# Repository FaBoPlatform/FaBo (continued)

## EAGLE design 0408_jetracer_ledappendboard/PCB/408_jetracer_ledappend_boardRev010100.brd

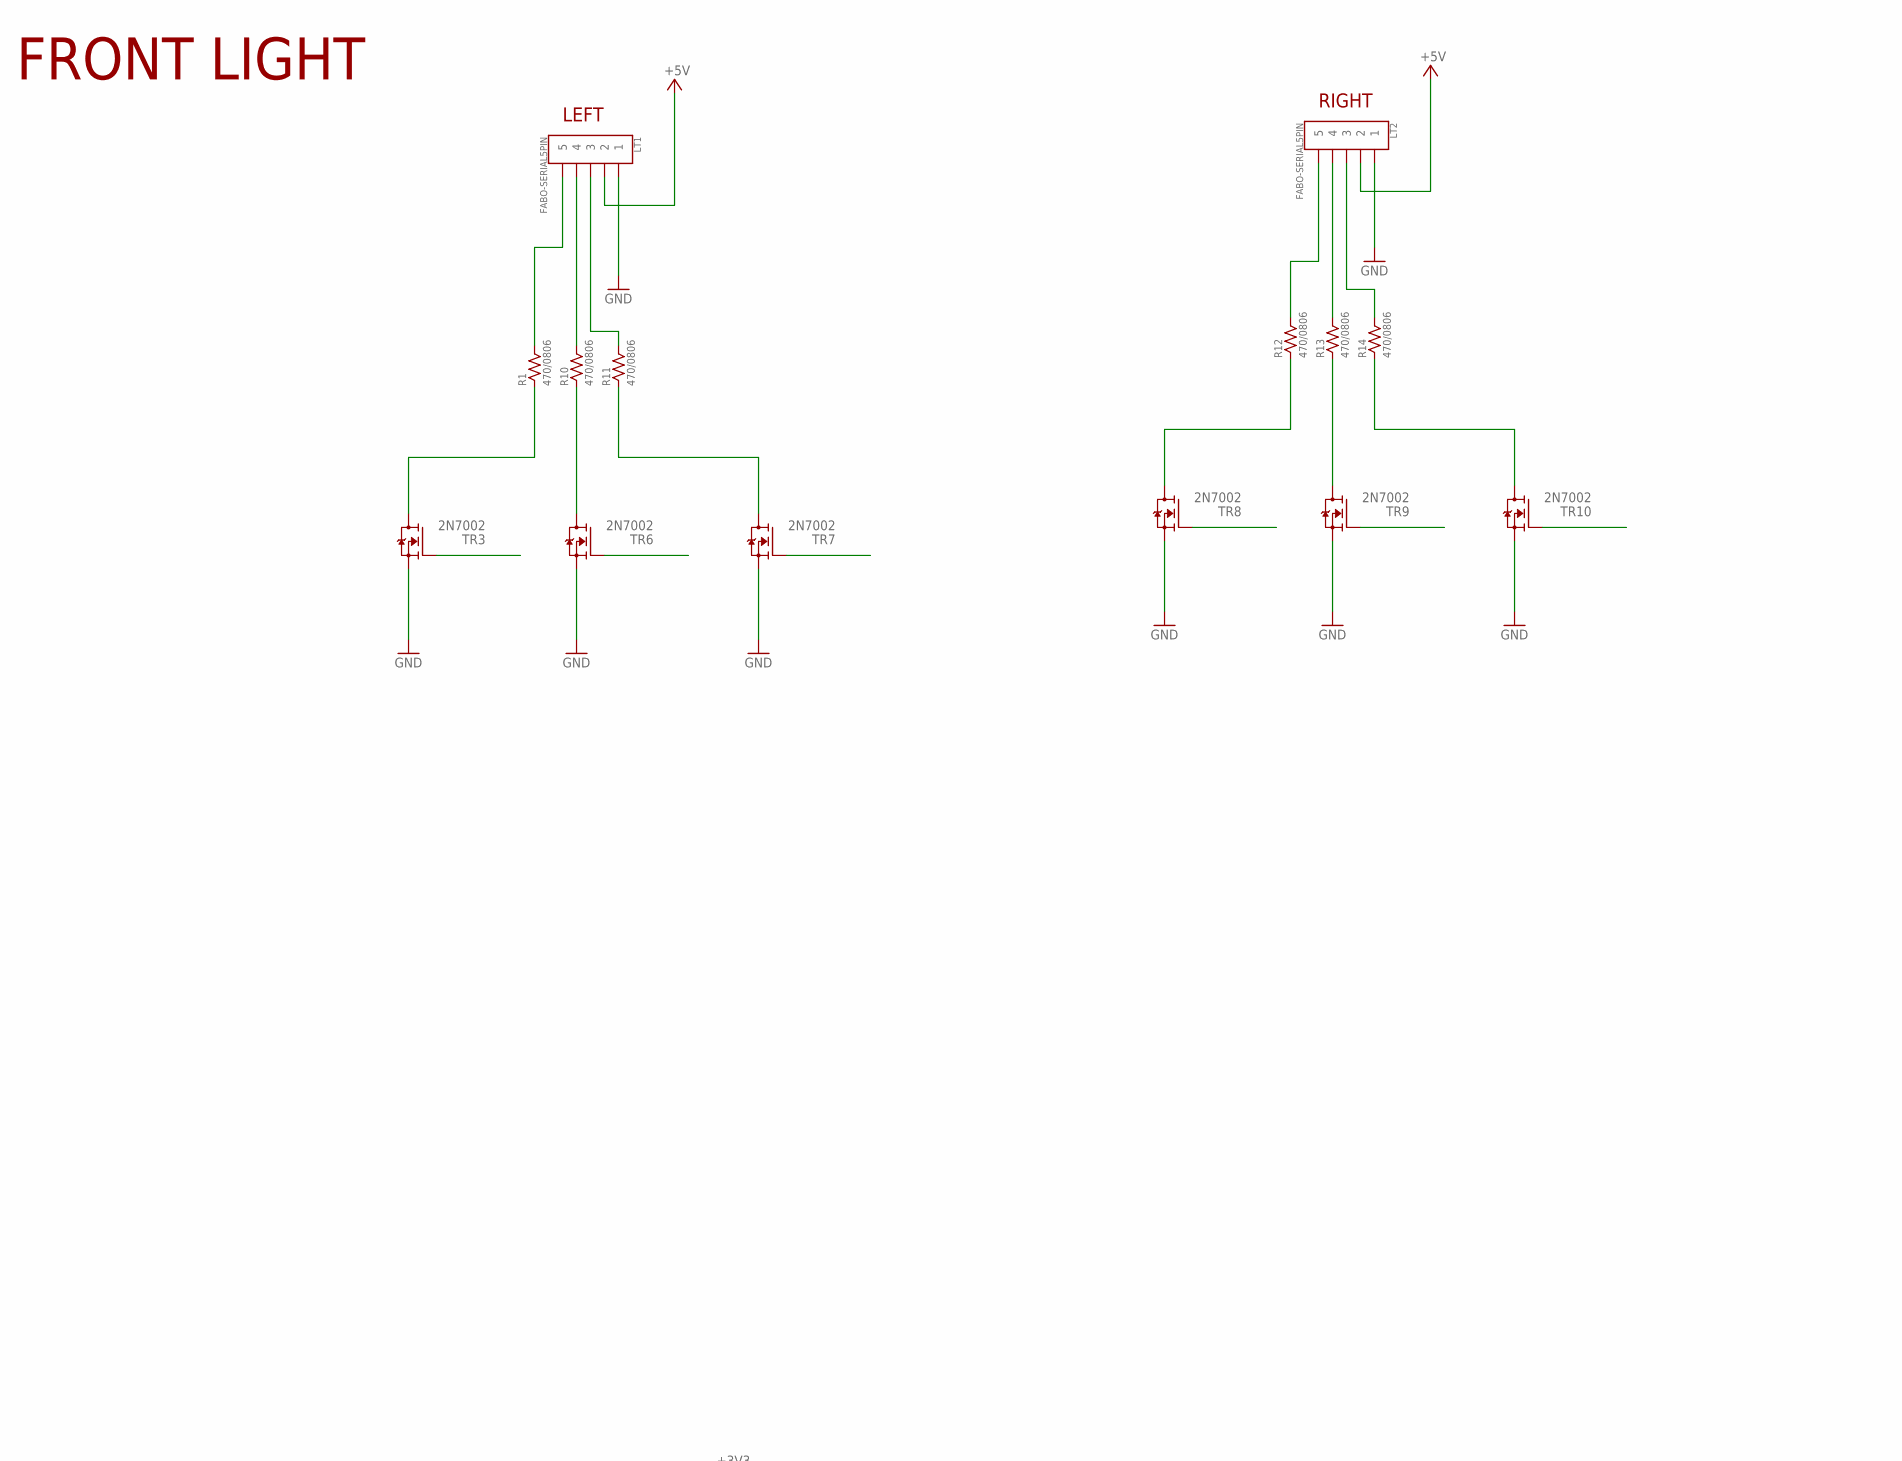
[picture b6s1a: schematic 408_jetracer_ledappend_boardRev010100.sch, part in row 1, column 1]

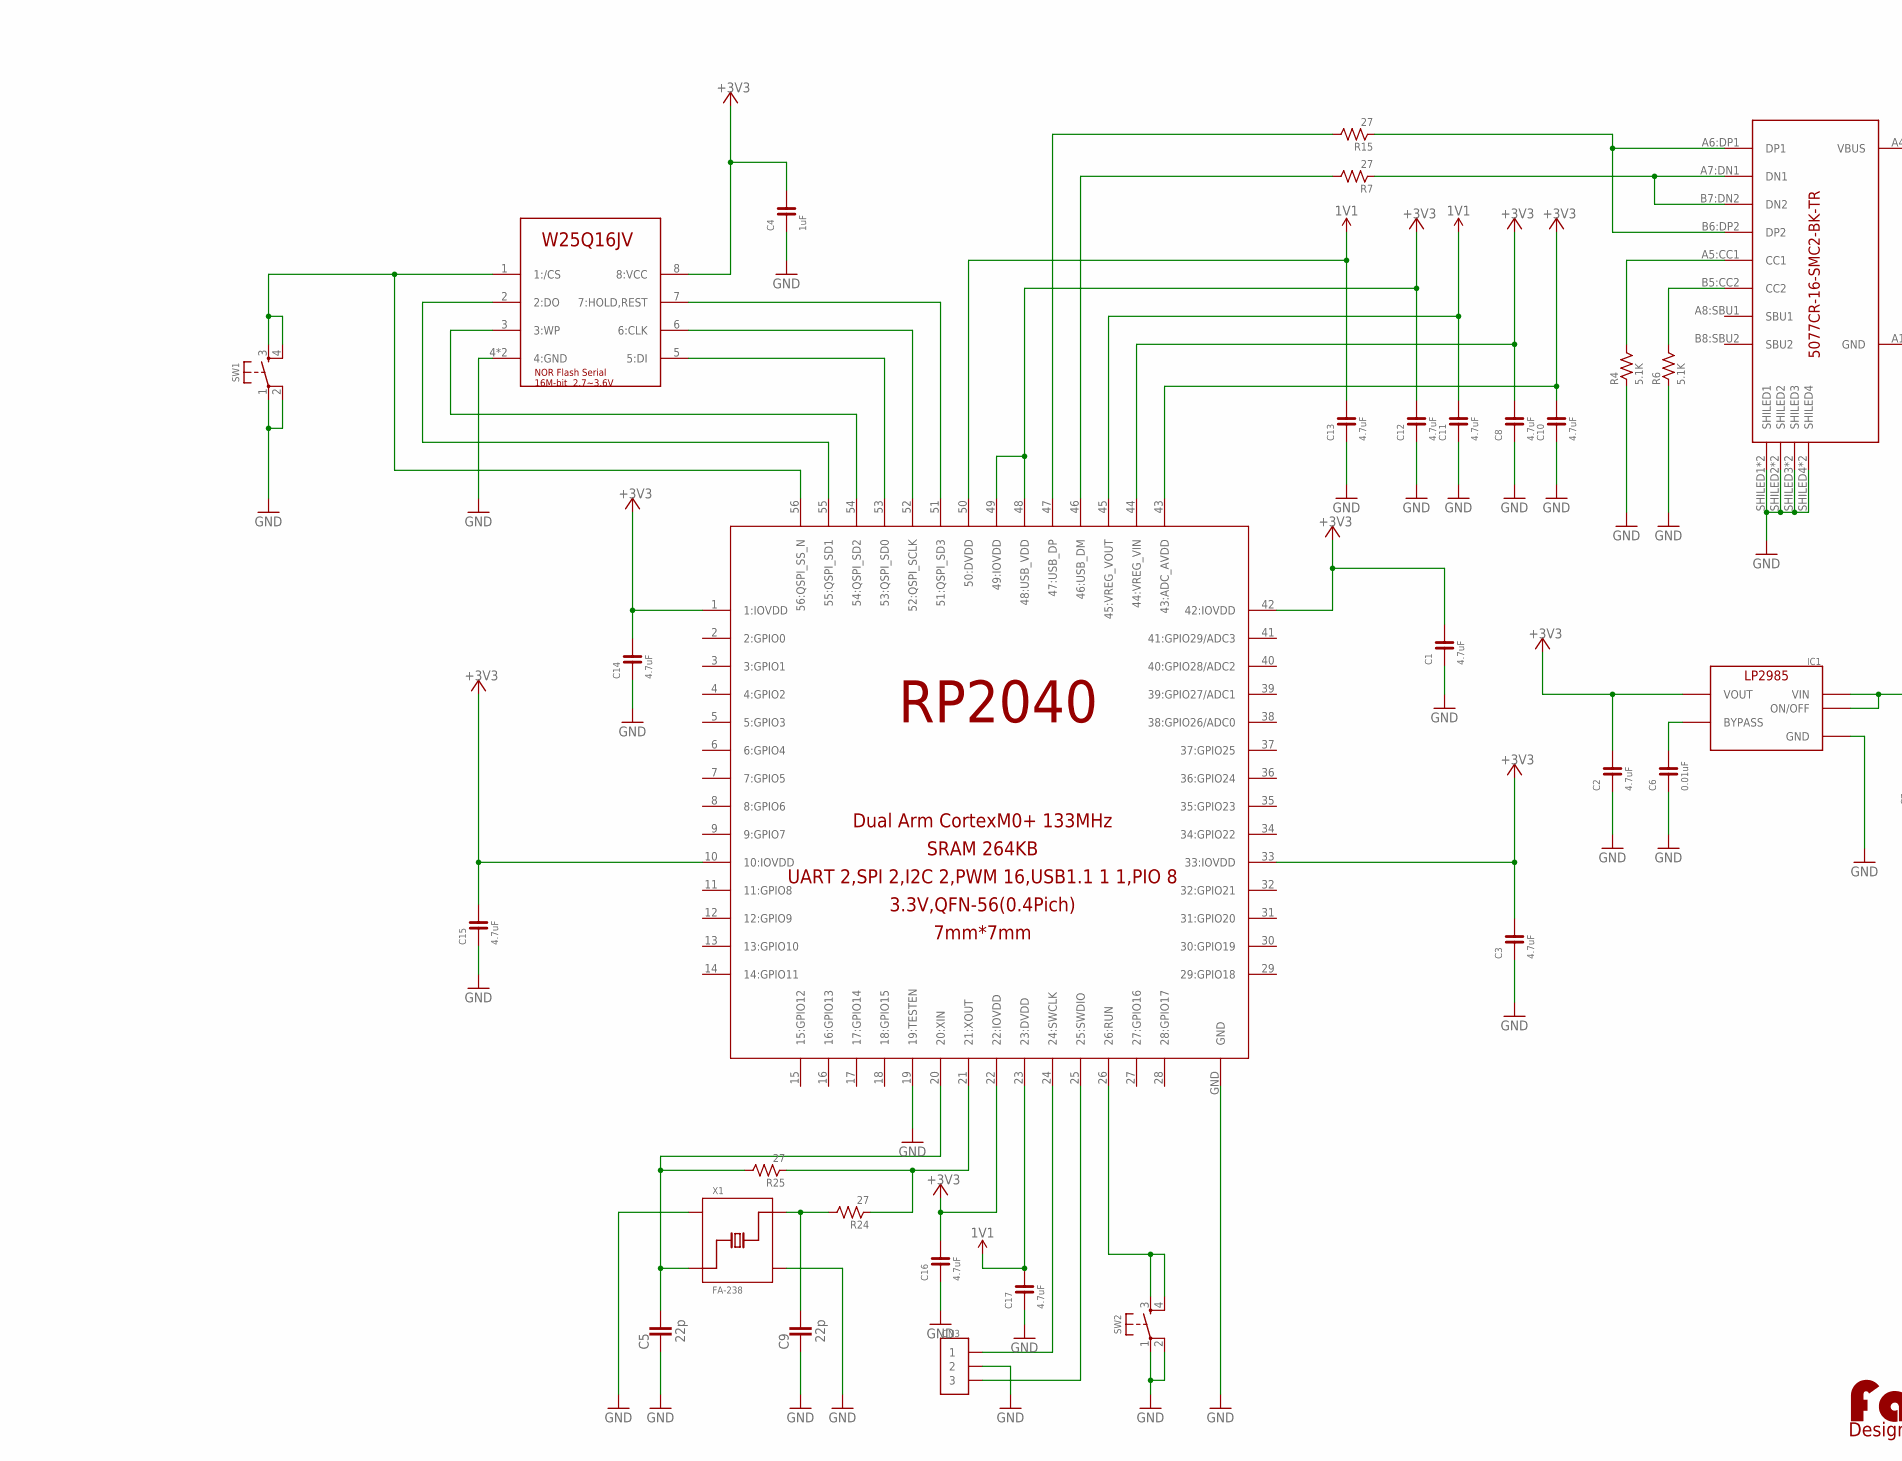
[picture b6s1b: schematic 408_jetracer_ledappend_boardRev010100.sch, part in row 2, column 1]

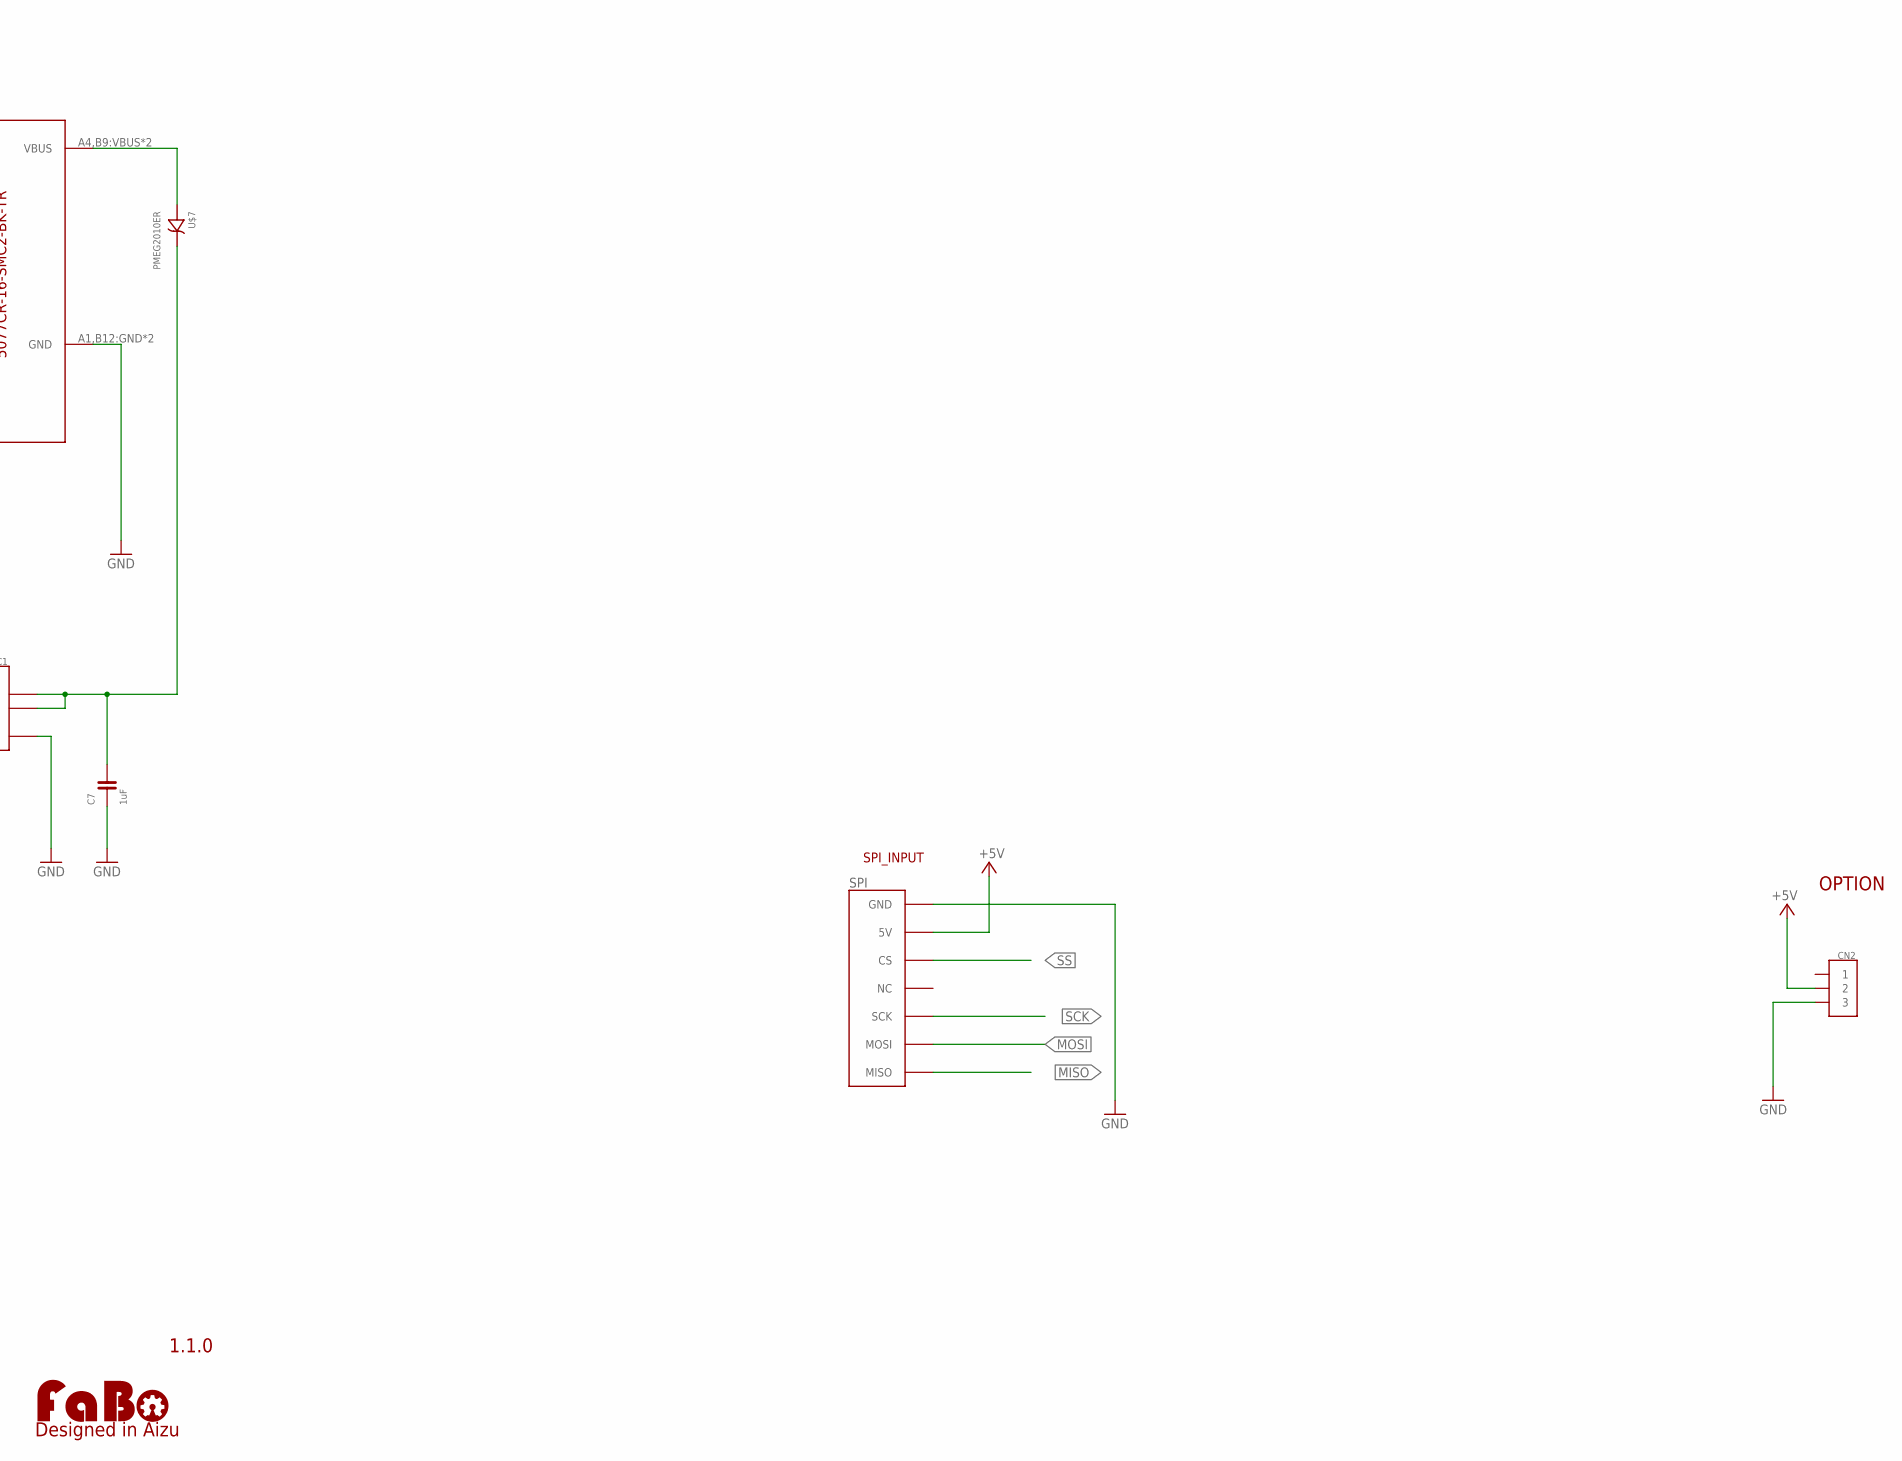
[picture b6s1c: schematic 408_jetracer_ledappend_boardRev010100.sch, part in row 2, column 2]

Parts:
C1, C2, C3, C8, C10, C11, C12, C13, C14, C15, C16, C17: 4.7uF; 0603
C4, C7: 1uF; 0603
C5, C9: 22p; C0603-ROUND
C6: 0.01uF; 0603
CN2, CN3: PIN_1X3
IC1: LP2985-33DBV; SOT-23-5
LOGO2: LOGO_FABO-M_BOTTOM; LOGO_FABO_M_BOTTOM
LT1, LT2: FABO-SERIAL5PIN; BM05B-PASS-1
R1, R10, R11, R12, R13, R14: 470/0806; 0805
R4, R6: 5.1K; 0603
R7, R15, R24, R25: 27; 0603
SPI: FABO-7PINMULTI_SPI; BM07B-PASS-1
SW1, SW2: TACT-SWITCH-SMD_KMR2; KMR2
TR3, TR6, TR7, TR8, TR9, TR10: 2N7002; SOT-23
U$2: RP2040
U$4: W25Q16JVZPIM; WSON8
U$6: 5077CR-16-SMC2-BK-TR
U$7: PMEG2010ER; SOD123W
X1: FA-238

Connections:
1V8: C11.2, C13.2, C17.2, U$2.23 (23:DVDD), U$2.45 (45:VREG_VOUT), U$2.50 (50:DVDD)
+3V3: C1.2, C2.2, C3.2, C4.2, C8.2, C10.2, C12.2, C14.2, C15.2, C16.2, IC1.5 (VOUT), U$2.1 (1:IOVDD), U$2.10 (10:IOVDD), U$2.22 (22:IOVDD), U$2.33 (33:IOVDD), U$2.42 (42:IOVDD), U$2.43 (43:ADC_AVDD), U$2.44 (44:VREG_VIN), U$2.48 (48:USB_VDD), U$2.49 (49:IOVDD), U$4.8 (8:VCC)
+5V: CN2.2, LT1.2, LT2.2, SPI.2 (5V)
GND: C1.1, C2.1, C3.1, C4.1, C5.1, C6.1, C7.1, C8.1, C9.1, C10.1, C11.1, C12.1, C13.1, C14.1, C15.1, C16.1, C17.1, CN2.3, CN3.2, IC1.2 (GND), LT1.1, LT2.1, R4.1, R6.1, SPI.1 (GND), SW1.1, SW1.2, SW2.1, SW2.2, TR3.2 (S), TR6.2 (S), TR7.2 (S), TR8.2 (S), TR9.2 (S), TR10.2 (S), U$2.19 (19:TESTEN), U$2.GND, U$4.4 (4:GND), U$4.PAD (4:GND), U$6.A1,B12:GND (GND), U$6.B1,A12:GND (GND), U$6.SHILED1, U$6.SHILED2, U$6.SHILED3, U$6.SHILED4, U$6.SHILED5 (SHILED1), U$6.SHILED6 (SHILED2), U$6.SHILED7 (SHILED3), U$6.SHILED8 (SHILED4), X1.2 (#2), X1.4 (#4)
MISO: SPI.7 (MISO)
MOSI: SPI.6 (MOSI)
unnamed: R13.1, TR9.1 (D)
unnamed: R10.1, TR6.1 (D)
unnamed: R1.1, TR3.1 (D)
unnamed: U$2.51 (51:QSPI_SD3), U$4.7 (7:HOLD,REST)
unnamed: R11.1, TR7.1 (D)
unnamed: LT1.5, R1.2
unnamed: C6.2, IC1.4 (BYPASS)
unnamed: R12.1, TR8.1 (D)
unnamed: LT1.4, R10.2
unnamed: TR3.3 (G), TR6.3 (G), TR7.3 (G), TR8.3 (G), TR9.3 (G), TR10.3 (G)
unnamed: LT1.3, R11.2
unnamed: LT2.5, R12.2
unnamed: LT2.4, R13.2
unnamed: LT2.3, R14.2
unnamed: R14.1, TR10.1 (D)
unnamed: U$2.52 (52:QSPI_SCLK), U$4.6 (6:CLK)
unnamed: U$2.53 (53:QSPI_SD0), U$4.5 (5:DI)
unnamed: C7.2, IC1.1 (VIN), IC1.3 (ON/OFF), U$7.1 (CATHODE)
unnamed: U$2.54 (54:QSPI_SD2), U$4.3 (3:WP)
unnamed: U$2.55 (55:QSPI_SD1), U$4.2 (2:DO)
unnamed: SW1.3, SW1.4, U$2.56 (56:QSPI_SS_N), U$4.1 (1:/CS)
unnamed: R7.2, U$2.46 (46:USB_DM)
unnamed: R15.2, U$2.47 (47:USB_DP)
unnamed: R4.2, U$6.A5:CC1 (CC1)
unnamed: R6.2, U$6.B5:CC2 (CC2)
unnamed: SW2.3, SW2.4, U$2.26 (26:RUN)
unnamed: R15.1, U$6.A6:DP1 (DP1), U$6.B6:DP2 (DP2)
unnamed: R7.1, U$6.A7:DN1 (DN1), U$6.B7:DN2 (DN2)
unnamed: C9.2, R24.2, X1.3 (#3)
unnamed: C5.2, R25.2, U$2.20 (20:XIN), X1.1 (#1)
unnamed: CN3.1, U$2.24 (24:SWCLK)
unnamed: R24.1, R25.1, U$2.21 (21:XOUT)
unnamed: CN3.3, U$2.25 (25:SWDIO)
SCK: SPI.5 (SCK)
SS: SPI.3 (CS)
VBUS: U$6.A4,B9:VBUS (VBUS), U$6.B4,A9:VBUS (VBUS), U$7.2 (ANODE)

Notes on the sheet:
1.1.0
SPI_INPUT
FRONT LIGHT
LEFT
RIGHT
OPTION

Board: 2 copper layers, 49 parts (1 on the bottom side), 38 nets, no tracks yet.
